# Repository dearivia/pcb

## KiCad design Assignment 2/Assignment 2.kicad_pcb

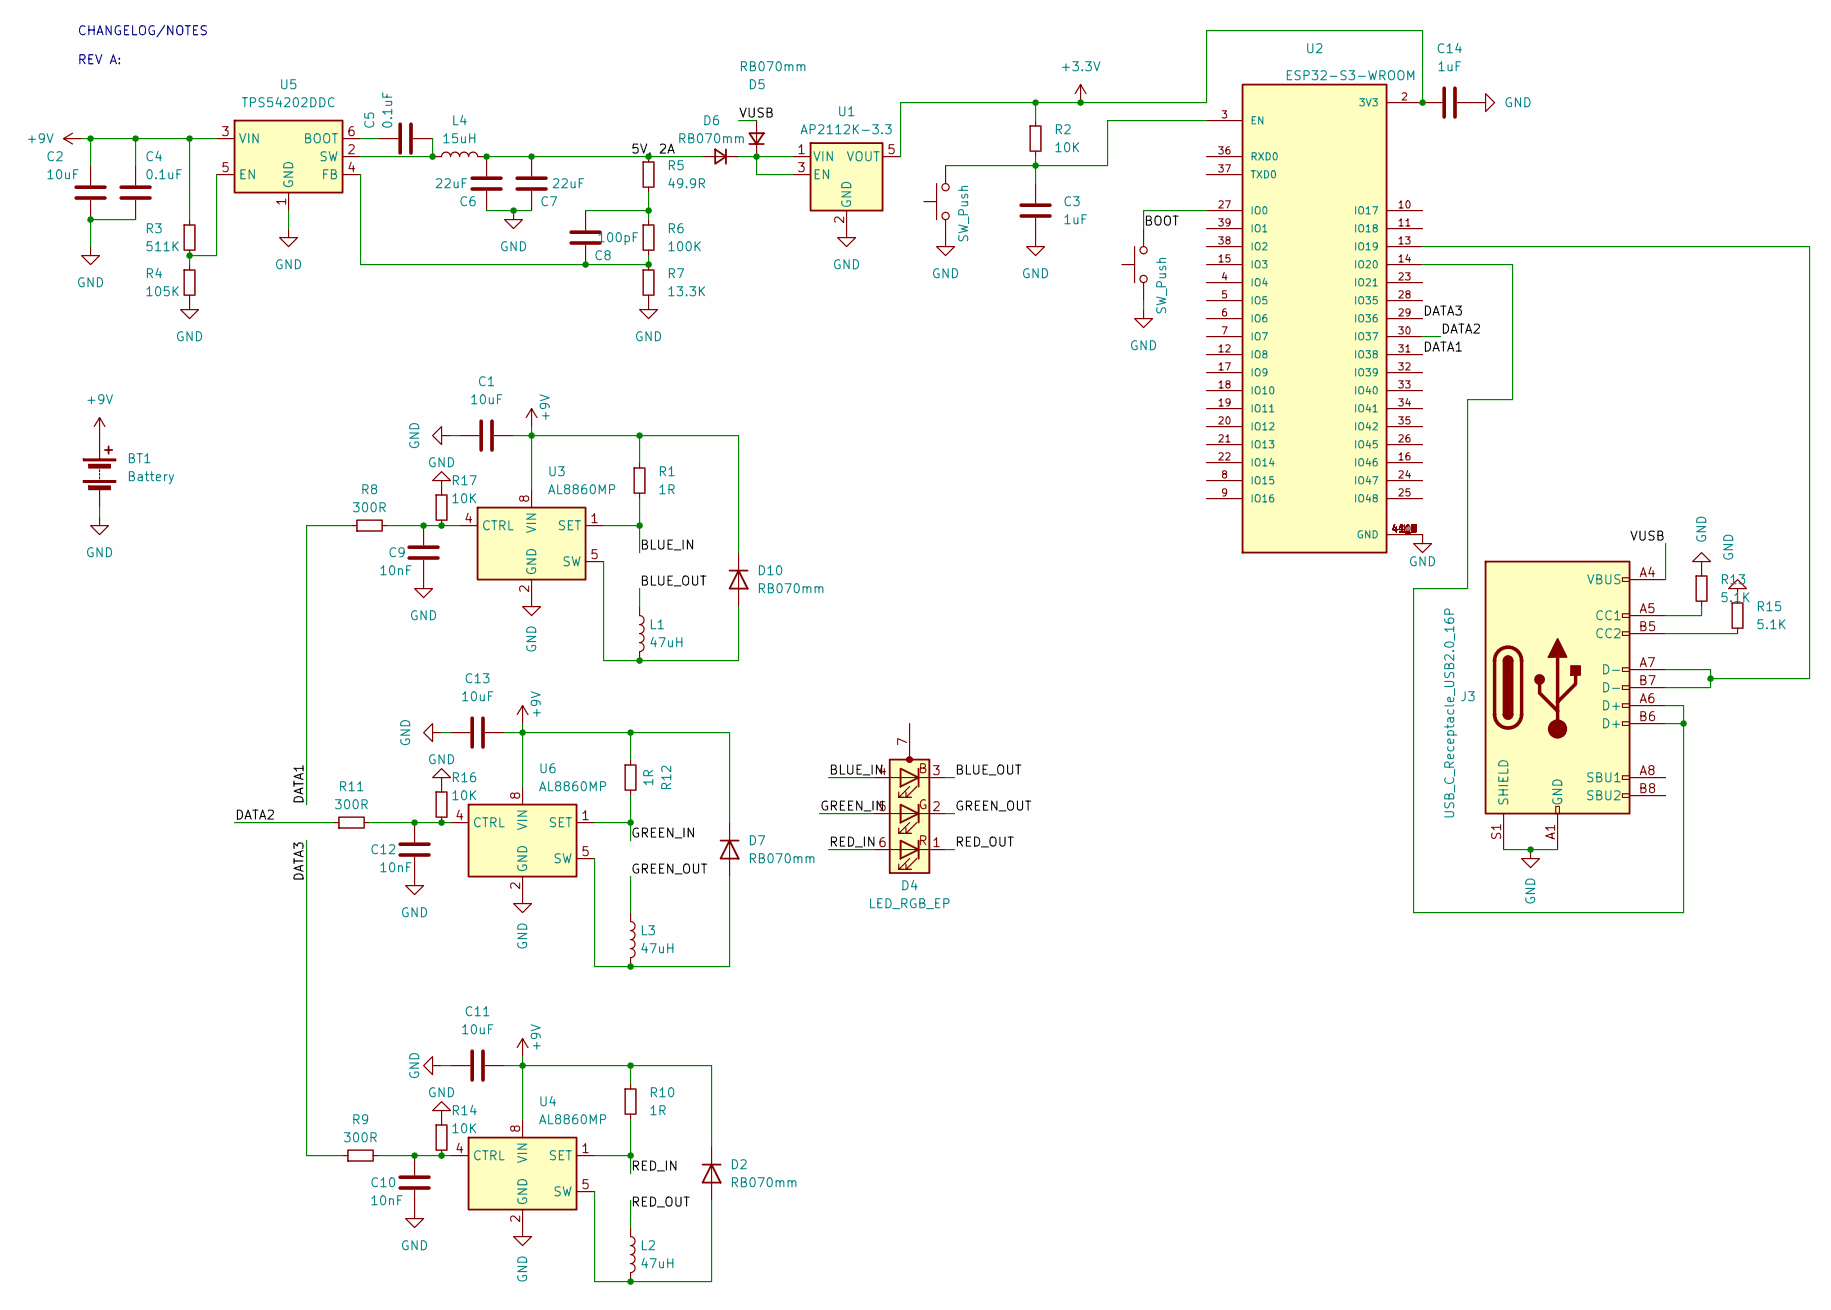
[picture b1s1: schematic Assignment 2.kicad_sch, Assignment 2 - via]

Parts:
BT1: Battery; BatteryHolder_MPD_BA9VPC_1xPP3
C1, C2, C11, C13: 10uF; C_1206_3216Metric
C3, C14: 1uF; C_0603_1608Metric
C4, C5: 0.1uF; C_0603_1608Metric
C6, C7: 22uF; C_0603_1608Metric
C8: 100pF; C_0603_1608Metric
C9, C10, C12: 10nF; C_0603_1608Metric
D2, D5, D6, D7, D10: RB070mm; D_SOD-123F; MPN RB070MM-30TFTR
D4: LED_RGB_EP; LED_RGB_Getian_GT-P6PRGB4303; MPN GT-P6PRGB430
J3: USB_C_Receptacle_USB2.0_16P; USB_C_Receptacle_GCT_USB4085; MPN USB4085
L1, L2, L3: 47uH; L_7.3x7.3_H4.5; MPN PA4302.473NLT
L4: 15uH; L_Bourns_SRR1208_12.7x12.7mm; MPN SRR1208-150ML
R1, R10, R12: 1R; R_0603_1608Metric
R2, R14, R16, R17: 10K; R_0603_1608Metric
R3: 511K; R_0603_1608Metric
R4: 105K; R_0603_1608Metric
R5: 49.9R; R_0603_1608Metric
R6: 100K; R_0603_1608Metric
R7: 13.3K; R_0603_1608Metric
R8, R9, R11: 300R; R_0603_1608Metric
R13, R15: 5.1K; R_0603_1608Metric
SW1, SW2: SW_Push; SW_Push_1P1T_NO_CK_KSC7xxJ; MPN D6C90 F2 LFS
U1: AP2112K-3.3; SOT-23-5; MPN AP2112K-3.3
U2: ESP32-S3-WROOM; ESP32-S3-WROOM-1; MPN ESP32-S3-WROOM
U3, U4, U6: AL8860MP; MSOP-8-1EP_3x3mm_P0.65mm_EP1.5x1.8mm; MPN AL8860MP
U5: TPS54202DDC; SOT-23-6; MPN TPS54202DDC

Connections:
+3.3V: C14.2, R2.1, U1.5 (VOUT), U2.2 (3V3)
+9V: BT1.1 (+), C1.1, C2.2, C4.2, C11.1, C13.1, D2.1 (K), D7.1 (K), D10.1 (K), R1.1, R3.1, R10.1, R12.1, U3.8 (VIN), U4.8 (VIN), U5.3 (VIN), U6.8 (VIN)
/5V, 2A: C6.1, C7.1, D6.2 (A), L4.2, R5.1
/BLUE_IN: D4.4 (BA), R1.2, U3.1 (SET)
/BLUE_OUT: D4.3 (BK), L1.1
/BOOT: SW2.2, U2.27 (IO0)
/DATA1: R8.1, U2.31 (IO38)
/DATA2: R11.1, U2.30 (IO37)
/DATA3: R9.1, U2.29 (IO36)
/GREEN_IN: D4.5 (GA), R12.2, U6.1 (SET)
/GREEN_OUT: D4.2 (GK), L3.1
/RED_IN: D4.6 (RA), R10.2, U4.1 (SET)
/RED_OUT: D4.1 (RK), L2.1
/VUSB: D5.2 (A), J3.A4 (VBUS), J3.A9 (VBUS), J3.B4 (VBUS), J3.B9 (VBUS)
GND: BT1.2 (-), C1.2, C2.1, C3.1, C4.1, C6.2, C7.2, C9.2, C10.2, C11.2, C12.2, C13.2, C14.1, J3.A1 (GND), J3.A12 (GND), J3.B1 (GND), J3.B12 (GND), J3.S1 (SHIELD), R4.2, R7.2, R13.1, R14.1, R15.1, R16.1, R17.1, SW1.1, SW2.1, U1.2 (GND), U2.1 (GND), U2.40 (GND), U2.41 (GND), U2.41_2 (GND), U2.41_3 (GND), U2.41_4 (GND), U2.41_5 (GND), U2.41_6 (GND), U2.41_7 (GND), U2.41_8 (GND), U2.41_9 (GND), U3.2 (GND), U3.3 (GND), U3.9 (GND), U4.2 (GND), U4.3 (GND), U4.9 (GND), U5.1 (GND), U6.2 (GND), U6.3 (GND), U6.9 (GND)
unnamed: C8.1, R5.2, R6.1
unnamed: D2.2 (A), L2.2, U4.5 (SW), U4.6 (SW)
unnamed: D5.1 (K), D6.1 (K), U1.1 (VIN), U1.3 (EN)
unnamed: D7.2 (A), L3.2, U6.5 (SW), U6.6 (SW)
unnamed: D10.2 (A), L1.2, U3.5 (SW), U3.6 (SW)
unnamed: J3.A5 (CC1), R13.2
unnamed: J3.B5 (CC2), R15.2
unnamed: C3.2, R2.2, SW1.2, U2.3 (EN)
unnamed: J3.A7 (D-), J3.B7 (D-), U2.13 (IO19)
unnamed: J3.A6 (D+), J3.B6 (D+), U2.14 (IO20)
unnamed: C9.1, R8.2, R17.2, U3.4 (CTRL)
unnamed: C10.1, R9.2, R14.2, U4.4 (CTRL)
unnamed: C5.2, U5.6 (BOOT)
unnamed: R3.2, R4.1, U5.5 (EN)
unnamed: C8.2, R6.2, R7.1, U5.4 (FB)
unnamed: C5.1, L4.1, U5.2 (SW)
unnamed: C12.1, R11.2, R16.2, U6.4 (CTRL)

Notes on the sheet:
CHANGELOG/NOTES REV A:

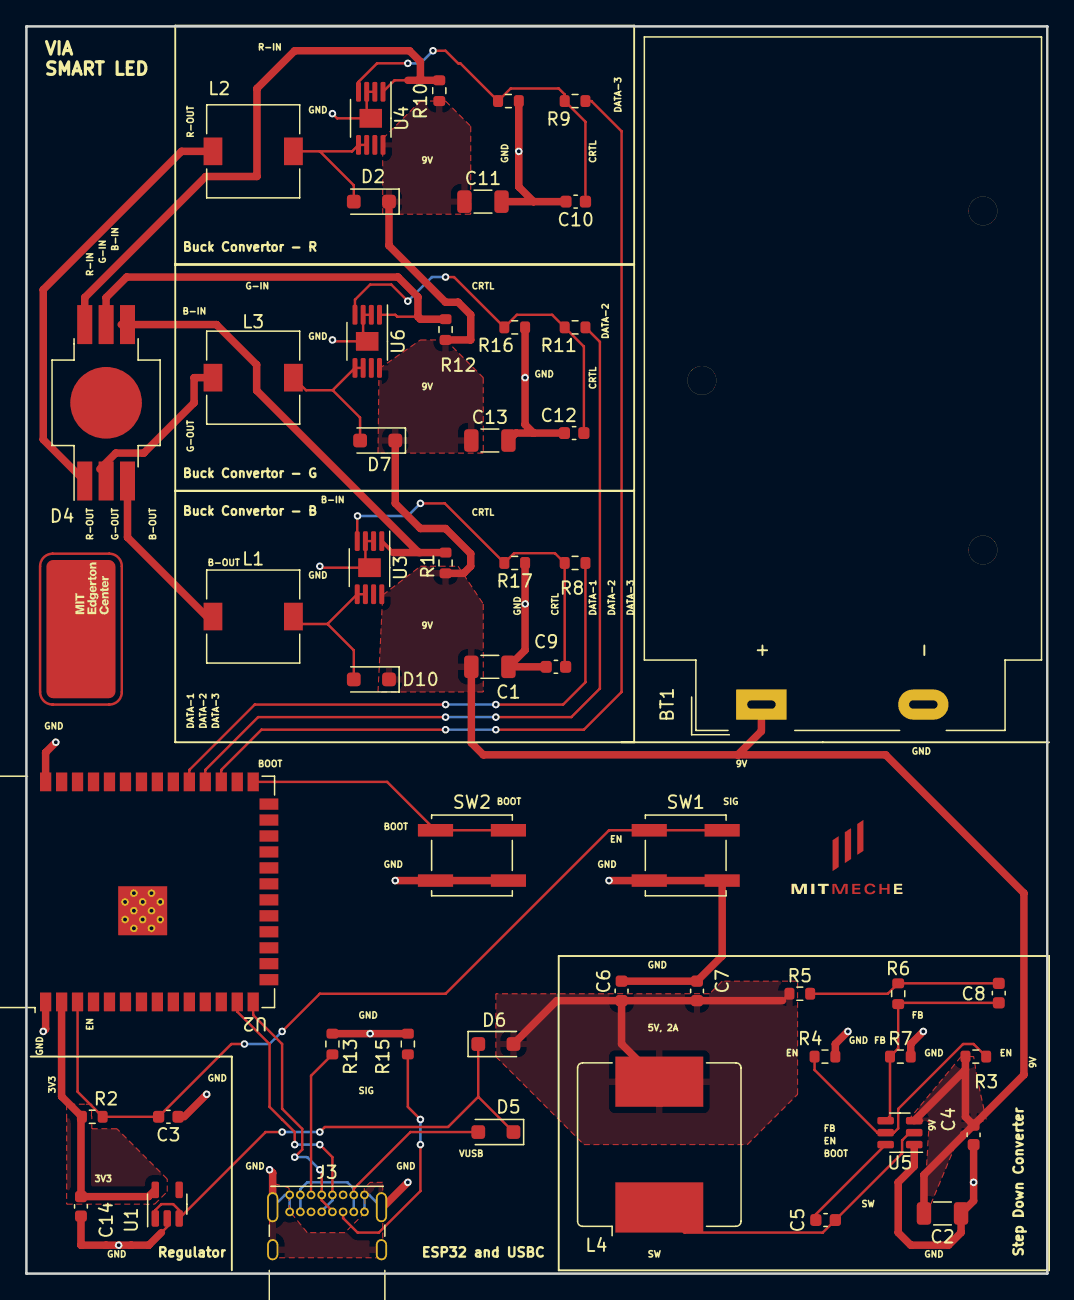
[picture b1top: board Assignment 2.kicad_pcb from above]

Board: 2 copper layers, 81.2 x 99.2 mm, 51 parts (0 on the bottom side), 32 nets.

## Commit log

2024-01-12 pelp
    assignment 2
2024-01-12 kull
    kull
2024-01-16 help
2024-01-17 kelp
2024-01-18 null
2024-01-19 ...
    its joever
2024-01-19 sob
    sdkjsjd
2024-01-19 bop
    ssd
2024-01-20 pcbbbb
    yayyy???
2024-01-20 sdsjd
2024-01-20 naur
    sds
2024-01-20 aggg
    s
2024-01-20 irp
    asdkjas
